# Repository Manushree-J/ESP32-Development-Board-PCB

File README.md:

<div align="center">

# 👋 Hi, I'm Manushree J

**Electronics & Communication Engineering Student**

Interested in Embedded Systems, Firmware Development, and PCB Design.

[LinkedIn Profile](https://www.linkedin.com/in/manushree-j-83086035a/)

</div>

---

## About Me

I'm an Electronics and Communication Engineering student who enjoys learning through hands-on engineering projects. I'm particularly interested in embedded systems, microcontroller-based development, and hardware design.

I believe in learning through experimentation, refining designs through multiple iterations, and understanding the engineering decisions behind each project.

---

# Custom ESP32 Development Board

**ESP32-WROOM-32E | KiCad 9 | Four-Layer PCB | CAN Interface**

A custom ESP32 development board developed through multiple PCB design iterations, progressing from an initial two-layer layout to a four-layer design. The current revision focuses on component-placement changes and further PCB layout refinement.

## 3D PCB Views

## Four-Layer PCB Layout

### 1. Front Copper — F.Cu

### 2. Inner Copper 1 — In1.Cu

### 3. Inner Copper 2 — In2.Cu

### 4. Back Copper — B.Cu

## Schematic

## Key Features

- ESP32-WROOM-32E microcontroller module
- USB-C connectivity with CP2102N USB-to-UART interface
- AMS1117-3.3 V voltage regulation
- GPIO expansion header
- BOOT and RESET buttons
- Onboard user LED
- SN65HVD230 CAN transceiver
- NUP2105L CAN bus protection
- Configurable 120 Ω CAN termination
- Three-pin CAN screw terminal
- Four corner mounting holes

## Design Evolution

This project documents three stages of development:

1. **Initial two-layer PCB:** Establishing the core ESP32 board architecture, USB connectivity, power supply, and GPIO access.
2. **Four-layer PCB:** Moving to a four-copper-layer stack-up.
3. **Current redesign:** Revisiting component placement and refining the overall layout, including the CAN interface.

The goal is to improve the design through iterative refinement and careful review of layout decisions.

## Engineering Work

- Schematic capture and component selection
- Footprint assignment and component placement
- Four-layer PCB stack-up and copper-layer layout
- Signal routing and copper-zone configuration
- Electrical Rule Check (ERC) and Design Rule Check (DRC)
- 3D visualization using KiCad
- Project documentation and version control using Git

## Project Status

**Ongoing — PCB design and layout refinement.**

The next steps include reviewing component placement and routing, checking design constraints, preparing the board for fabrication, and validating the assembled hardware.

Fabrication and physical hardware validation have not yet been completed.

## Tools Used

`KiCad 9` · `ESP32-WROOM-32E` · `CP2102N` · `SN65HVD230` · `NUP2105L` · `Git`

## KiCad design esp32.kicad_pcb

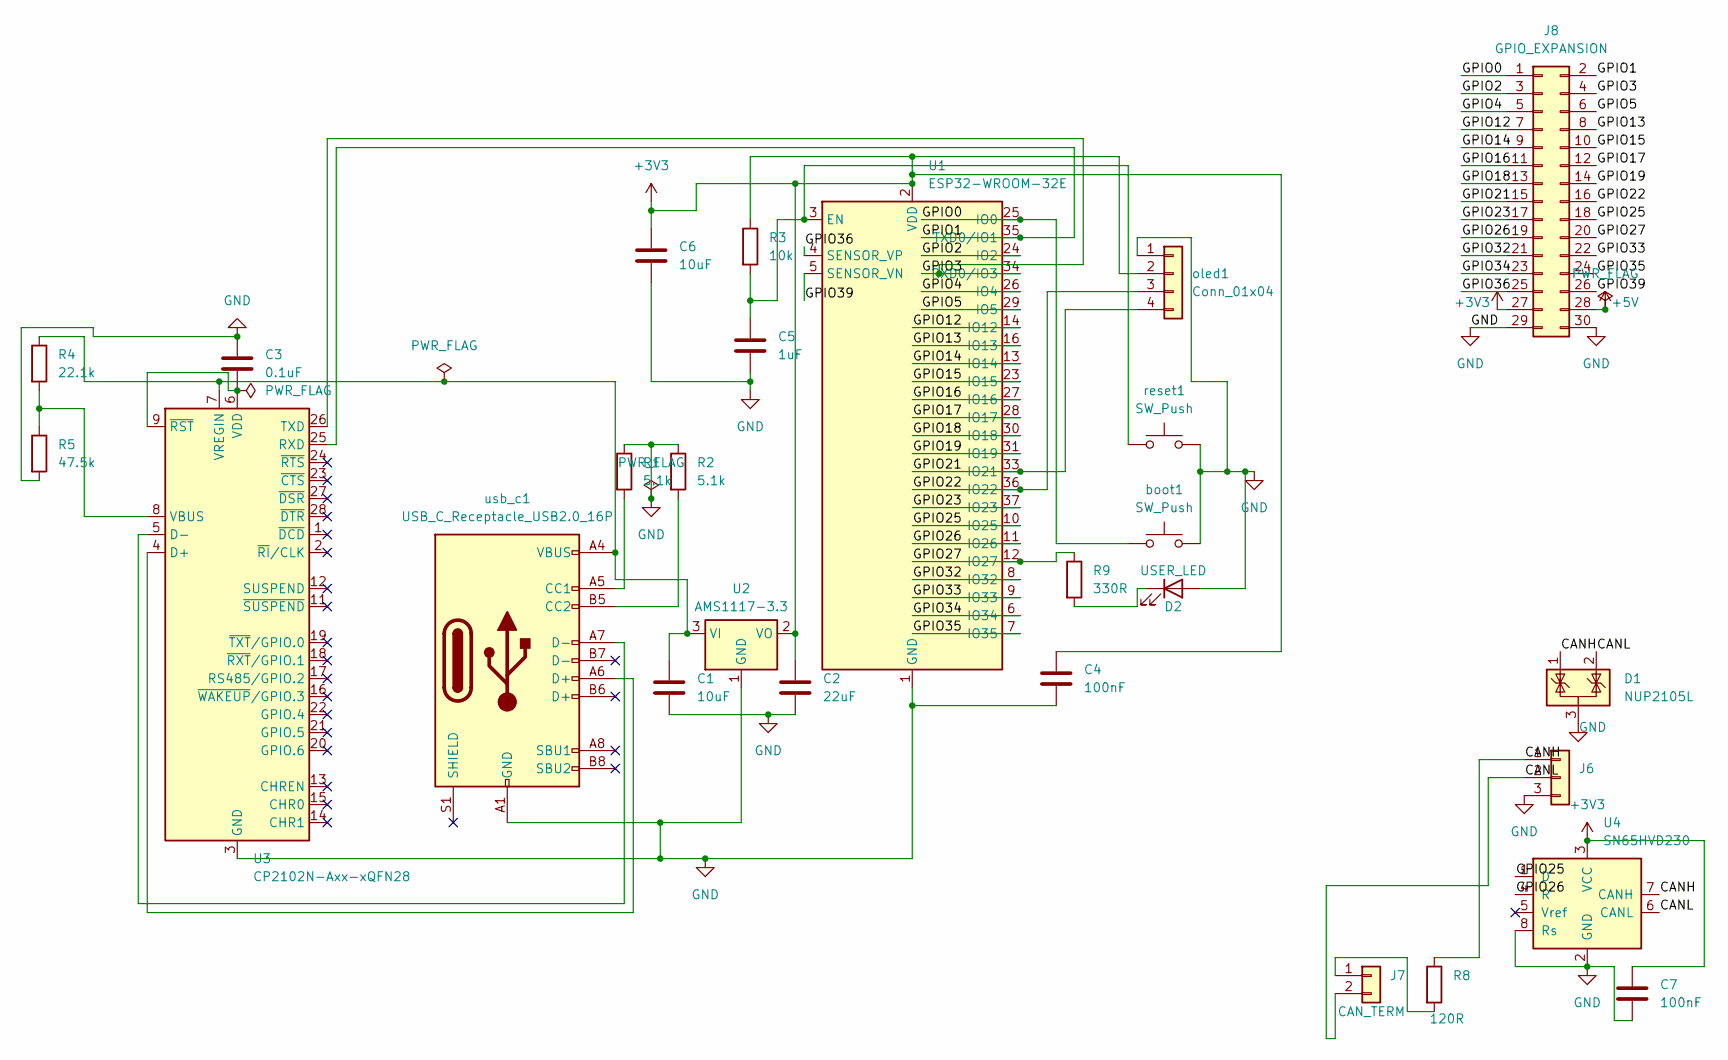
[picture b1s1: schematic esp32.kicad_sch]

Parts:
C1, C6: 10uF; C_0805_2012Metric
C2: 22uF; C_0805_2012Metric
C3: 0.1uF; C_0805_2012Metric
C4, C7: 100nF; C_0805_2012Metric
C5: 1uF; C_0805_2012Metric
D1: NUP2105L; SOT-23
D2: USER_LED; LED_0805_2012Metric
J6: CAN; PinHeader_1x03_P2.54mm_Vertical
J7: CAN_TERM; PinHeader_1x02_P2.54mm_Vertical
J8: GPIO_EXPANSION; PinHeader_2x15_P2.54mm_Vertical
R1, R2: 5.1k; R_0805_2012Metric
R3: 10k; R_0805_2012Metric
R4: 22.1k; R_0805_2012Metric
R5: 47.5k; R_0805_2012Metric
R8: 120R; R_0805_2012Metric
R9: 330R; R_0805_2012Metric
U1: ESP32-WROOM-32E
U2: AMS1117-3.3; SOT-223-3_TabPin2
U3: CP2102N-Axx-xQFN28; QFN-28-1EP_5x5mm_P0.5mm_EP3.35x3.35mm
U4: SN65HVD230; SOIC-8_3.9x4.9mm_P1.27mm
boot1: SW_Push; SW_PUSH_6mm
oled1: Conn_01x04; PinHeader_1x04_P2.54mm_Vertical
reset1: SW_Push; SW_PUSH_6mm
usb_c1: USB_C_Receptacle_USB2.0_16P; USB_C_Receptacle_GCT_USB4105-xx-A_16P_TopMnt_Horizontal

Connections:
+3V3: C2.1, C4.1, C6.1, C7.1, J8.27, R3.1, U1.2 (VDD), U2.2 (VO), U4.3 (VCC), oled1.2
+5V: J8.28
/CANH: D1.1 (K), J6.1, R8.1, U4.7 (CANH)
/CANL: D1.2 (K), J6.2, J7.2, U4.6 (CANL)
/GPIO0: J8.1, U1.25 (IO0), boot1.1
/GPIO1: J8.2, U1.35 (TXD0/IO1), U3.25 (RXD)
/GPIO2: J8.3, U1.24 (IO2)
/GPIO3: J8.4, U1.34 (RXD0/IO3), U3.26 (TXD)
/GPIO4: J8.5, U1.26 (IO4)
/GPIO5: J8.6, U1.29 (IO5)
/GPIO12: J8.7, U1.14 (IO12)
/GPIO13: J8.8, U1.16 (IO13)
/GPIO14: J8.9, U1.13 (IO14)
/GPIO15: J8.10, U1.23 (IO15)
/GPIO16: J8.11, U1.27 (IO16)
/GPIO17: J8.12, U1.28 (IO17)
/GPIO18: J8.13, U1.30 (IO18)
/GPIO19: J8.14, U1.31 (IO19)
/GPIO21: J8.15, U1.33 (IO21), oled1.4
/GPIO22: J8.16, U1.36 (IO22), oled1.3
/GPIO23: J8.17, U1.37 (IO23)
/GPIO25: J8.18, U1.10 (IO25), U4.1 (D)
/GPIO26: J8.19, U1.11 (IO26), U4.4 (R)
/GPIO27: J8.20, R9.1, U1.12 (IO27)
/GPIO32: J8.21, U1.8 (IO32)
/GPIO33: J8.22, U1.9 (IO33)
/GPIO34: J8.23, U1.6 (IO34)
/GPIO35: J8.24, U1.7 (IO35)
/GPIO36: J8.25, U1.4 (SENSOR_VP)
/GPIO39: J8.26, U1.5 (SENSOR_VN)
GND: C1.2, C2.2, C3.1, C4.2, C5.2, C6.2, C7.2, D1.3 (A), D2.2 (A), J6.3, J8.29, J8.30, R1.1, R2.1, R5.2, U1.1 (GND), U1.15 (GND), U1.38 (GND), U1.39 (GND), U2.1 (GND), U3.3 (GND), U3.29 (GND), U4.2 (GND), U4.8 (Rs), boot1.2, oled1.1, reset1.2, usb_c1.A1 (GND), usb_c1.A12 (GND), usb_c1.B1 (GND), usb_c1.B12 (GND)
unnamed: D2.1 (K), R9.2
unnamed: J7.1, R8.2
unnamed: C5.1, R3.2, U1.3 (EN), reset1.1
unnamed: C1.1, R4.1, U2.3 (VI), U3.7 (VREGIN), usb_c1.A4 (VBUS), usb_c1.A9 (VBUS), usb_c1.B4 (VBUS), usb_c1.B9 (VBUS)
unnamed: U3.4 (D+), usb_c1.A6 (D+)
unnamed: U3.5 (D-), usb_c1.A7 (D-)
unnamed: R4.2, R5.1, U3.8 (VBUS)
unnamed: C3.2, U3.6 (VDD), U3.9 (~RST)
unnamed: R1.2, usb_c1.A5 (CC1)
unnamed: R2.2, usb_c1.B5 (CC2)

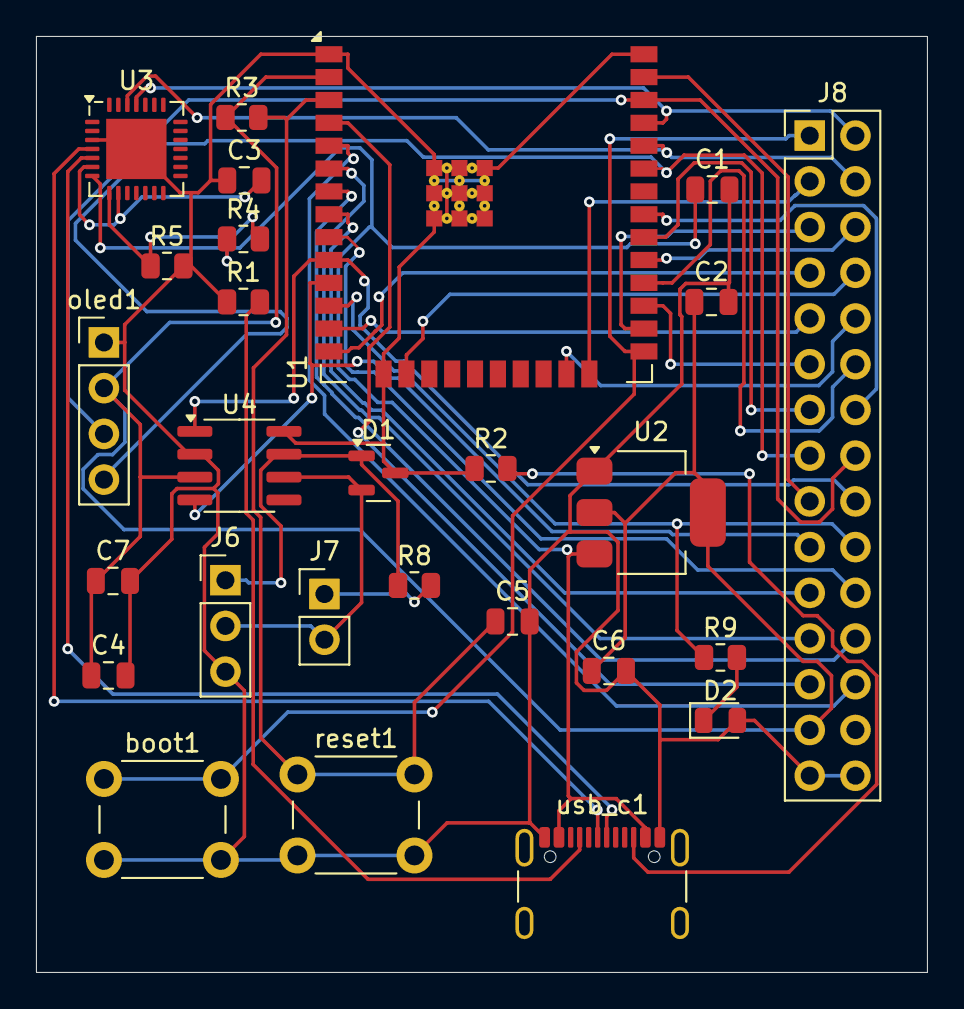
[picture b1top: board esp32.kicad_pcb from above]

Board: 2 copper layers, 49.5 x 52.0 mm, 27 parts (0 on the bottom side), 40 nets.
